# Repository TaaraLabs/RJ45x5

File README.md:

1-Wire Passive 5-port HUB
=========================

[WebSite](https://taaralabs.eu/ob1)

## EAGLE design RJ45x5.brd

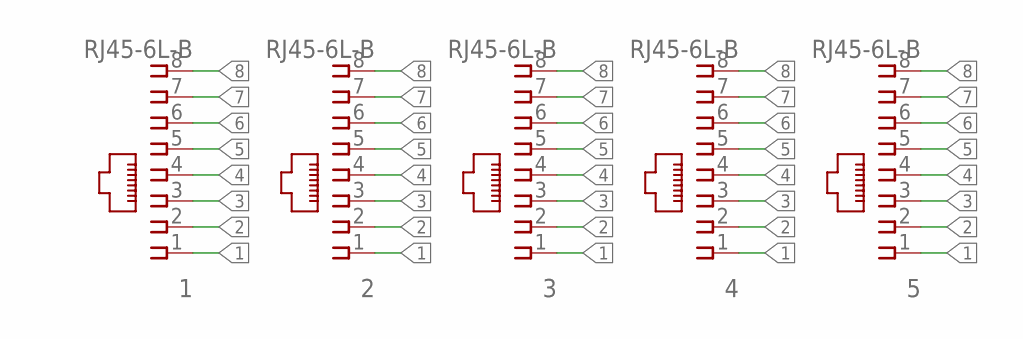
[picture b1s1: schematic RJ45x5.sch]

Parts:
1, 2, 3, 4, 5: RJ45-6L-B; RJ45-NO-SHIELD

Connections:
1: 1.1, 2.1, 3.1, 4.1, 5.1
2: 1.2, 2.2, 3.2, 4.2, 5.2
3: 1.3, 2.3, 3.3, 4.3, 5.3
4: 1.4, 2.4, 3.4, 4.4, 5.4
5: 1.5, 2.5, 3.5, 4.5, 5.5
6: 1.6, 2.6, 3.6, 4.6, 5.6
7: 1.7, 2.7, 3.7, 4.7, 5.7
8: 1.8, 2.8, 3.8, 4.8, 5.8

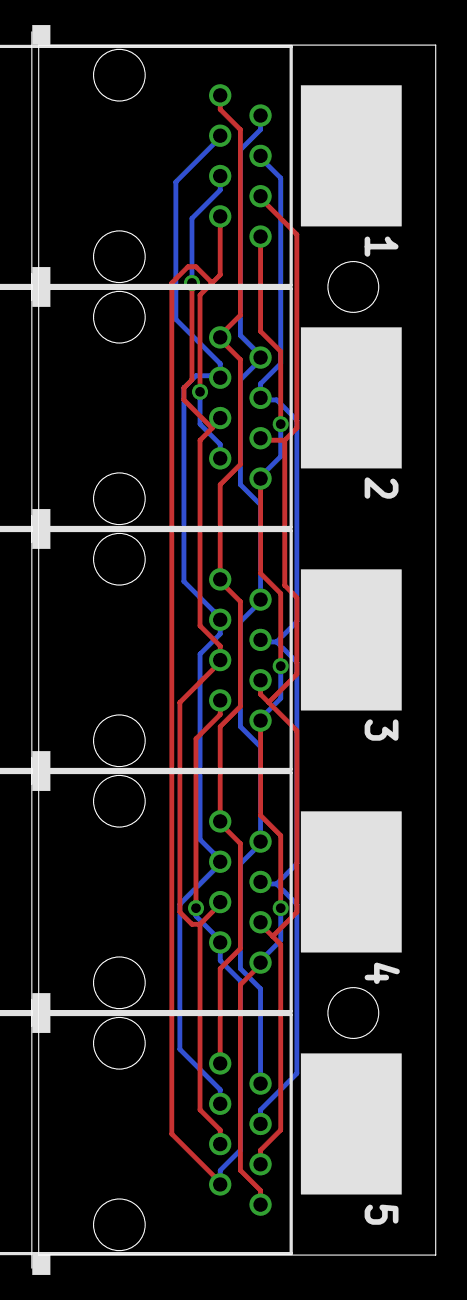
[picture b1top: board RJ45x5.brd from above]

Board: 2 copper layers, 25.4 x 77.9 mm, 6 parts (1 on the bottom side), 8 nets.

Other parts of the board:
U$1: OSHW-LOGO-M

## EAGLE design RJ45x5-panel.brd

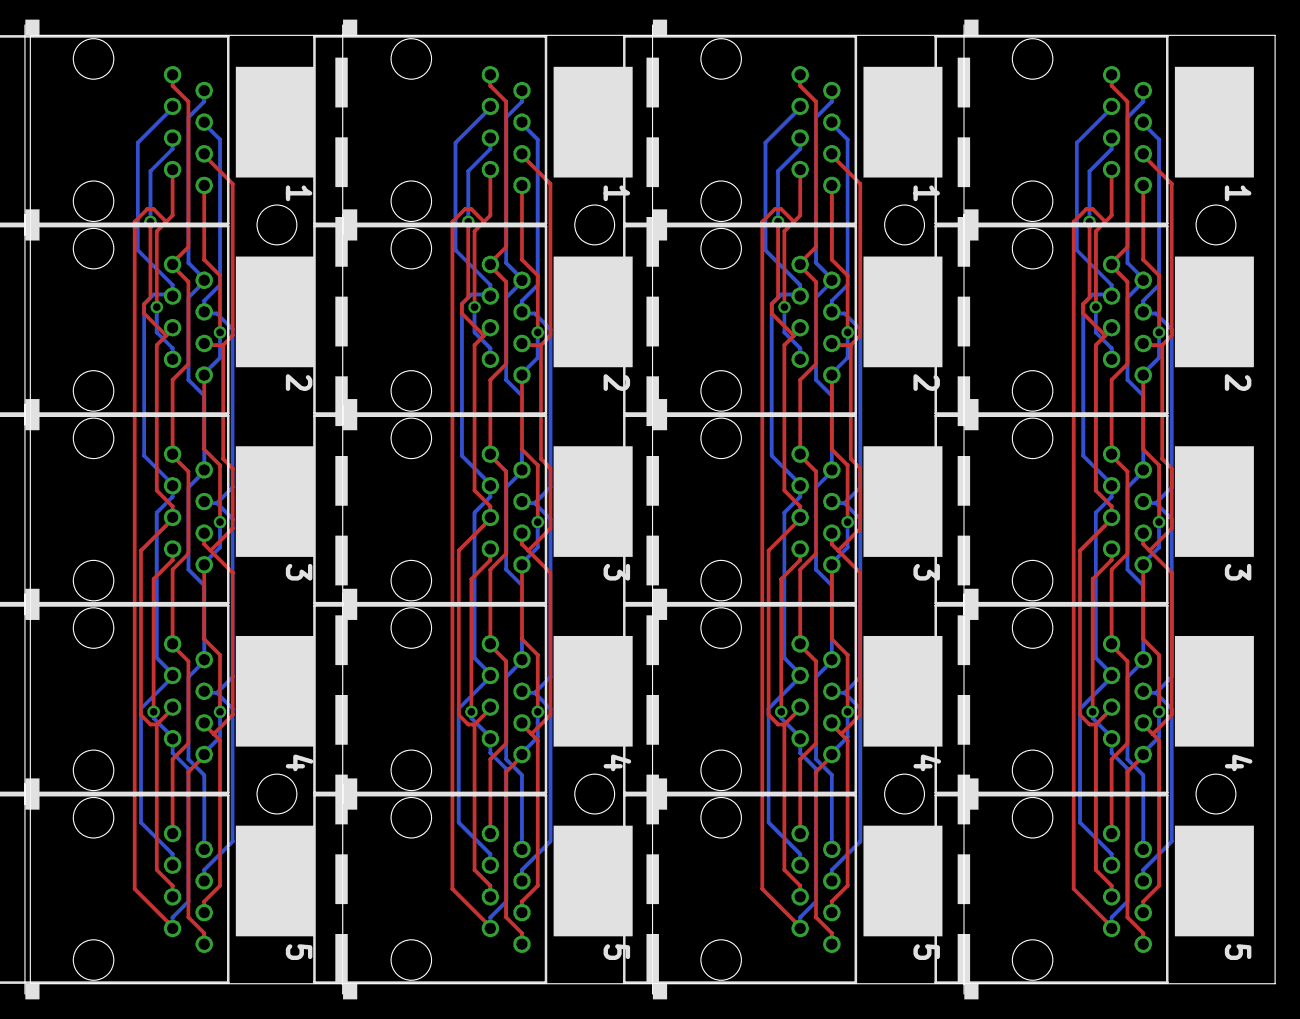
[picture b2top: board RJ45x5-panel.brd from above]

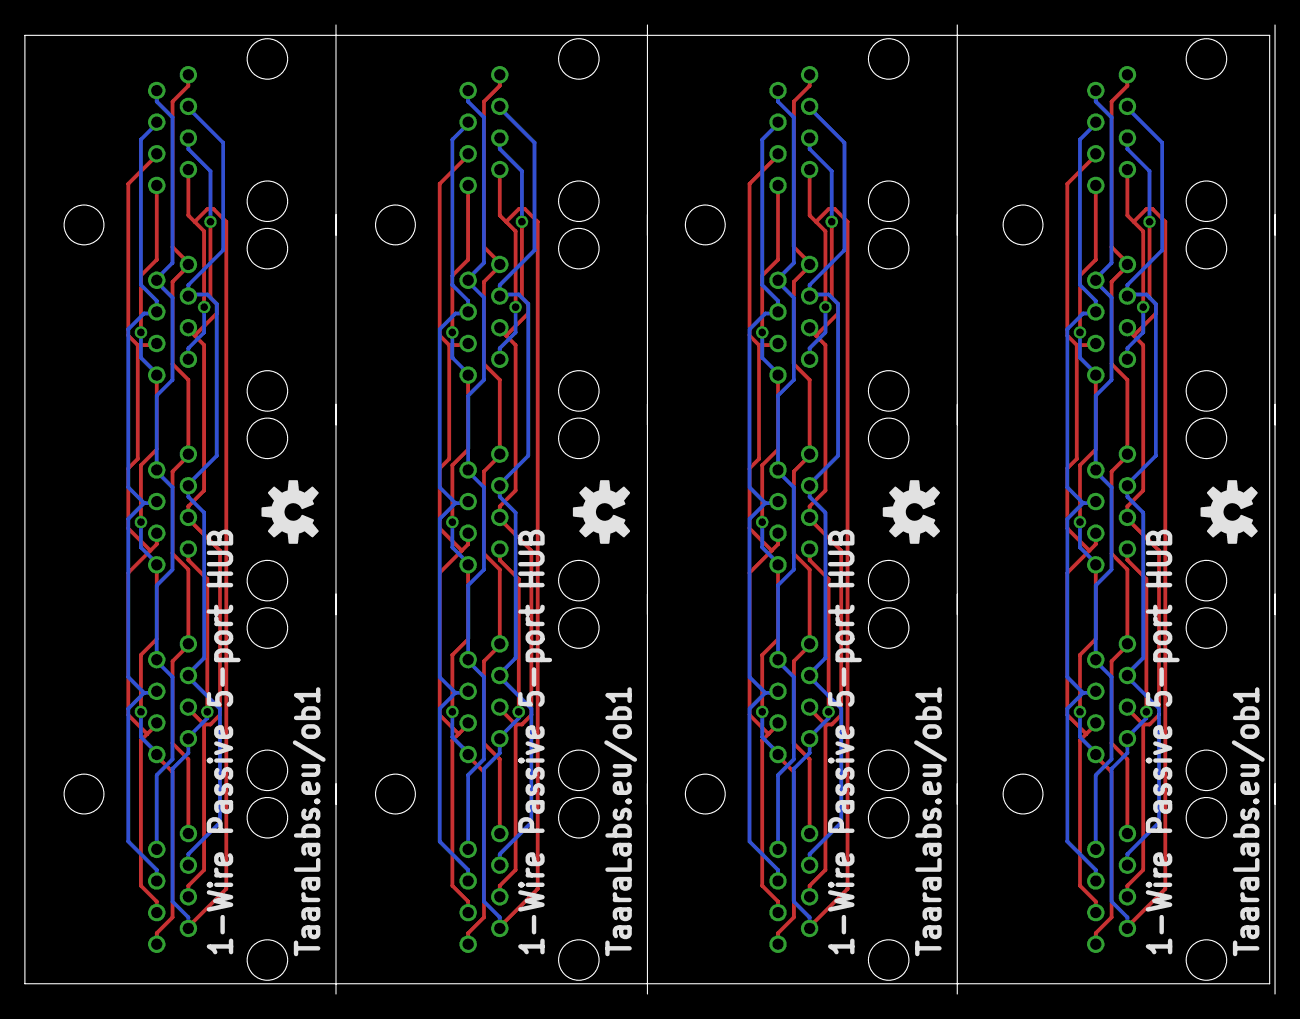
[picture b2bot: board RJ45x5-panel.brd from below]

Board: 2 copper layers, 100.4 x 77.9 mm, 24 parts (4 on the bottom side), 32 nets.

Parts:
1, 2, 3, 4, 5, 6, 7, 8, 9, 10, 11, 12, 13, 14, 15, 16, 17, 18, 19, 20: RJ45-6L-B; RJ45-NO-SHIELD
U$1, U$2, U$3, U$4: OSHW-LOGO-M

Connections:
1: 1.1, 2.1, 3.1, 4.1, 5.1
2: 1.2, 2.2, 3.2, 4.2, 5.2
3: 1.3, 2.3, 3.3, 4.3, 5.3
4: 1.4, 2.4, 3.4, 4.4, 5.4
5: 1.5, 2.5, 3.5, 4.5, 5.5
6: 1.6, 2.6, 3.6, 4.6, 5.6
7: 1.7, 2.7, 3.7, 4.7, 5.7
8: 1.8, 2.8, 3.8, 4.8, 5.8
9: 6.1, 7.1, 8.1, 9.1, 10.1
10: 6.2, 7.2, 8.2, 9.2, 10.2
11: 6.3, 7.3, 8.3, 9.3, 10.3
12: 6.4, 7.4, 8.4, 9.4, 10.4
13: 6.5, 7.5, 8.5, 9.5, 10.5
14: 6.6, 7.6, 8.6, 9.6, 10.6
15: 6.7, 7.7, 8.7, 9.7, 10.7
16: 6.8, 7.8, 8.8, 9.8, 10.8
17: 11.1, 12.1, 13.1, 14.1, 15.1
18: 11.2, 12.2, 13.2, 14.2, 15.2
19: 11.3, 12.3, 13.3, 14.3, 15.3
20: 11.4, 12.4, 13.4, 14.4, 15.4
21: 11.5, 12.5, 13.5, 14.5, 15.5
22: 11.6, 12.6, 13.6, 14.6, 15.6
23: 11.7, 12.7, 13.7, 14.7, 15.7
24: 11.8, 12.8, 13.8, 14.8, 15.8
25: 16.1, 17.1, 18.1, 19.1, 20.1
26: 16.2, 17.2, 18.2, 19.2, 20.2
27: 16.3, 17.3, 18.3, 19.3, 20.3
28: 16.4, 17.4, 18.4, 19.4, 20.4
29: 16.5, 17.5, 18.5, 19.5, 20.5
30: 16.6, 17.6, 18.6, 19.6, 20.6
31: 16.7, 17.7, 18.7, 19.7, 20.7
32: 16.8, 17.8, 18.8, 19.8, 20.8

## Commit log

2016-04-29 initial upload

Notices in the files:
parts and their libraries:
SparkFun: Licensing: CC v3.0 Share-Alike You are welcome to use this library for commercial purposes.
